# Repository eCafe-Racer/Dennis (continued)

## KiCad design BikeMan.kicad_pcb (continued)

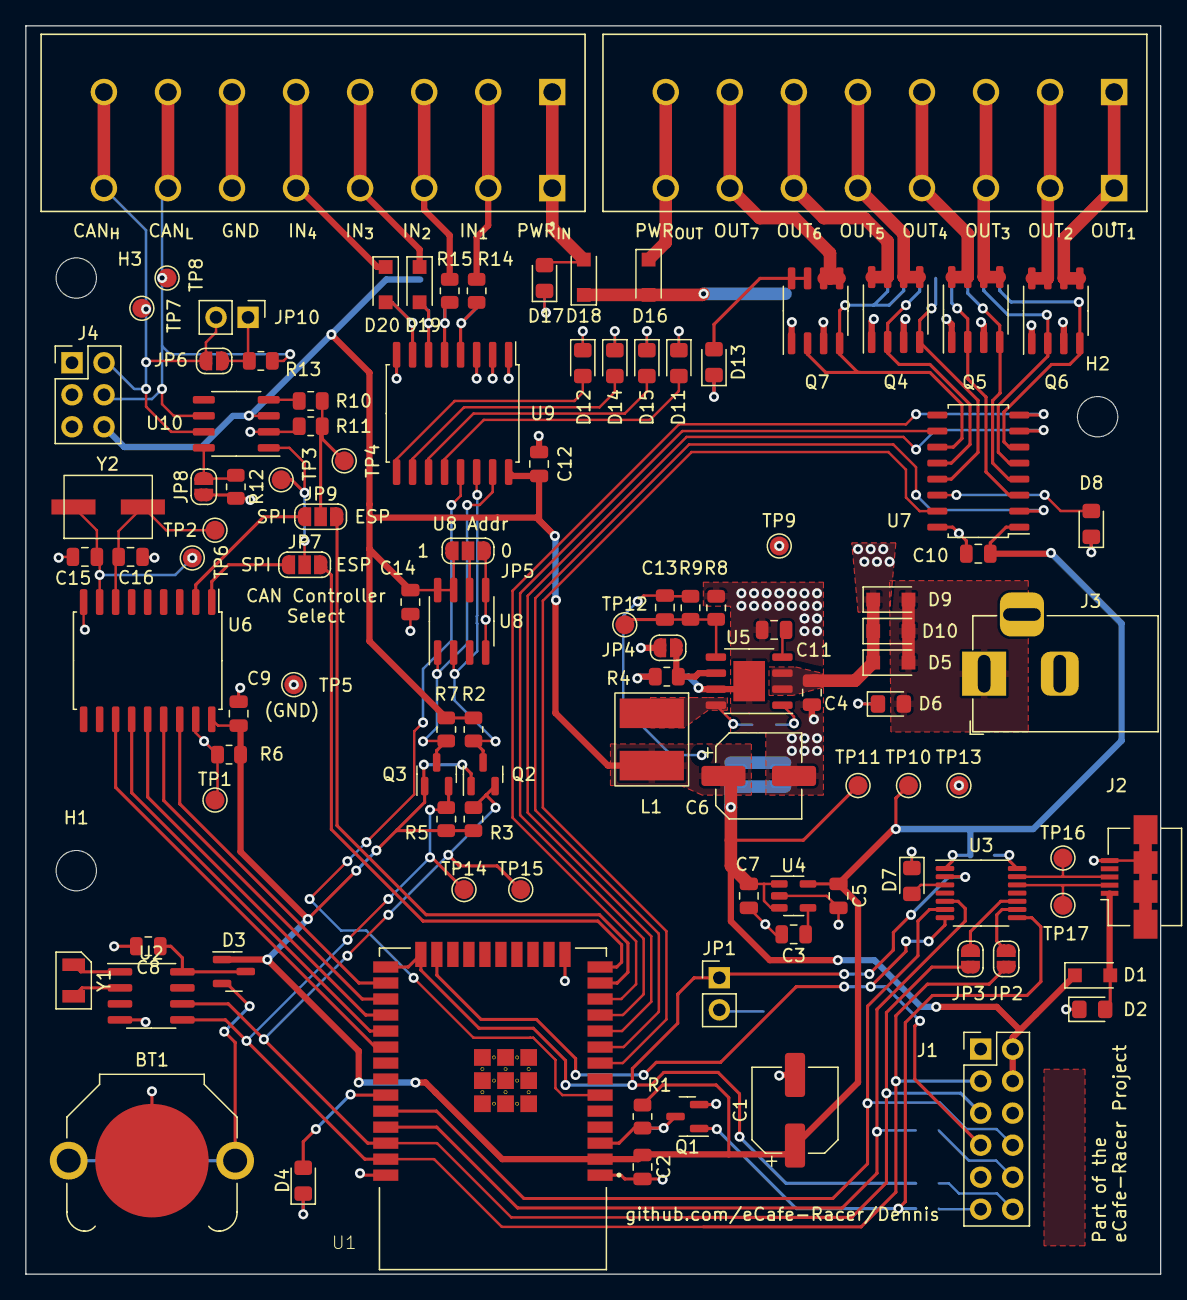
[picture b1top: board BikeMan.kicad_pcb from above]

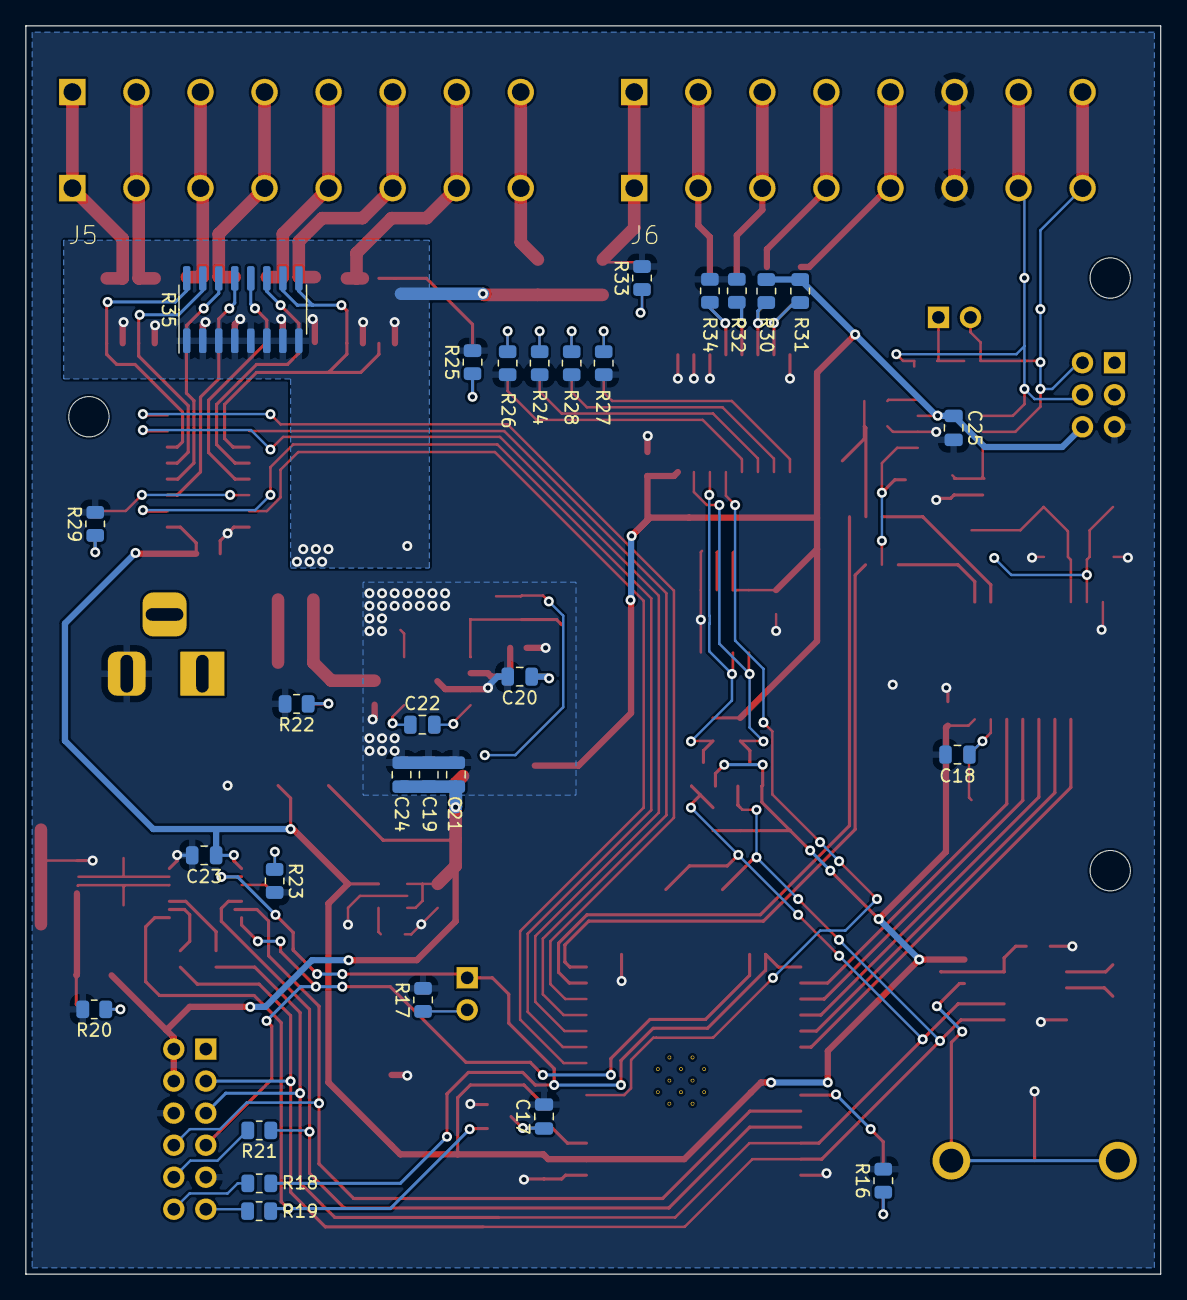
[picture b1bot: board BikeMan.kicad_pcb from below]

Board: 2 copper layers, 90.0 x 99.0 mm, 137 parts (29 on the bottom side), 105 nets.

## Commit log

2020-11-28 created project
2020-12-18 Migrated to KiCad 6.0
2020-12-29 Added 12V GPIO module
2020-12-29 Added LC values and inductor part number to buck converter circuit
2020-12-29 Added annotated reference numbers
2020-12-29 minor changes to project
2020-12-29 added backup folder to gitignore
2020-12-29 Finished CAN peripheral
2020-12-31 Real Time Clock circuit
2020-12-31 added HDMI connector
2020-12-31 Changes to top level schematic
2020-12-31 Added USB hub IC
2020-12-31 Deleted leftover files from old file format
2020-12-31 visual tweaks to schematic
2020-12-31 cleaning up workspace
2020-12-31 default BOM config file
2020-12-31 Messed with the schematic page border
2020-12-31 Added buses and USB ports to schematic
2020-12-31 Plotted Schematic for v0.1.1
2021-01-19 Added connector for ethernet
2021-01-19 unclear
2021-01-20 SD card circuits
2021-01-21 footprints
2021-01-21 starting layout
2021-01-22 Adding footprints and step files for connectors
2021-02-04 footprint assignments
2021-02-05 WIP 5 FEB 2021
2021-02-18 switched to networked resistors on GPIO system
2021-02-26 Added Daughter Card
2021-02-26 Documentation for v0.1.2
2021-03-02 more layout: power supply and gpio
2021-03-20 Routing for HDMI, Ethernet, SD Card, CAN
2021-03-20 documentation archive for 0.1.2
2021-03-22 Finished trace routing
2021-03-30 Cleaning up
    Reassigned reference designators to better match their position on the board.
    Moved USB hub IC and related circuits to their own sheet in the schematic.
    Tweaked reference designator positions on board to improve visibility.
2021-03-30 Documentation for v0.1.3
    Plotted schematic and generated images of board from several angles
2021-08-03 migrated computers
2021-08-03 removed Compute Module
2021-08-03 tweaked CAN interface
2021-08-03 started cleaning layout
2021-08-04 layout sketching
2021-08-05 components group and placed in roughly the right position
2021-08-06 finished routing
2021-08-06 geographical reannotate
2021-08-06 added test points and cleaned up silk screen
2021-08-06 updated 3d models
2021-08-07 cleaned up schematic
2021-08-07 updated page layout file
2021-08-07 documentation for v0.2.1
2021-08-07 Forgot to connect the interrupt signal for the GPIO
2021-08-07 worked on the readme
2021-08-08 gerbers for 0.2
